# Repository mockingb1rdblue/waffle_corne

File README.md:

## Modified Corne Light PCB 
* Support for [EVQWGD001](https://www.aliexpress.com/i/4001293888953.html) horizontal encoders
* Updated Alps switch footprints to use per-key LEDs 
* PCBs have not been tested yet

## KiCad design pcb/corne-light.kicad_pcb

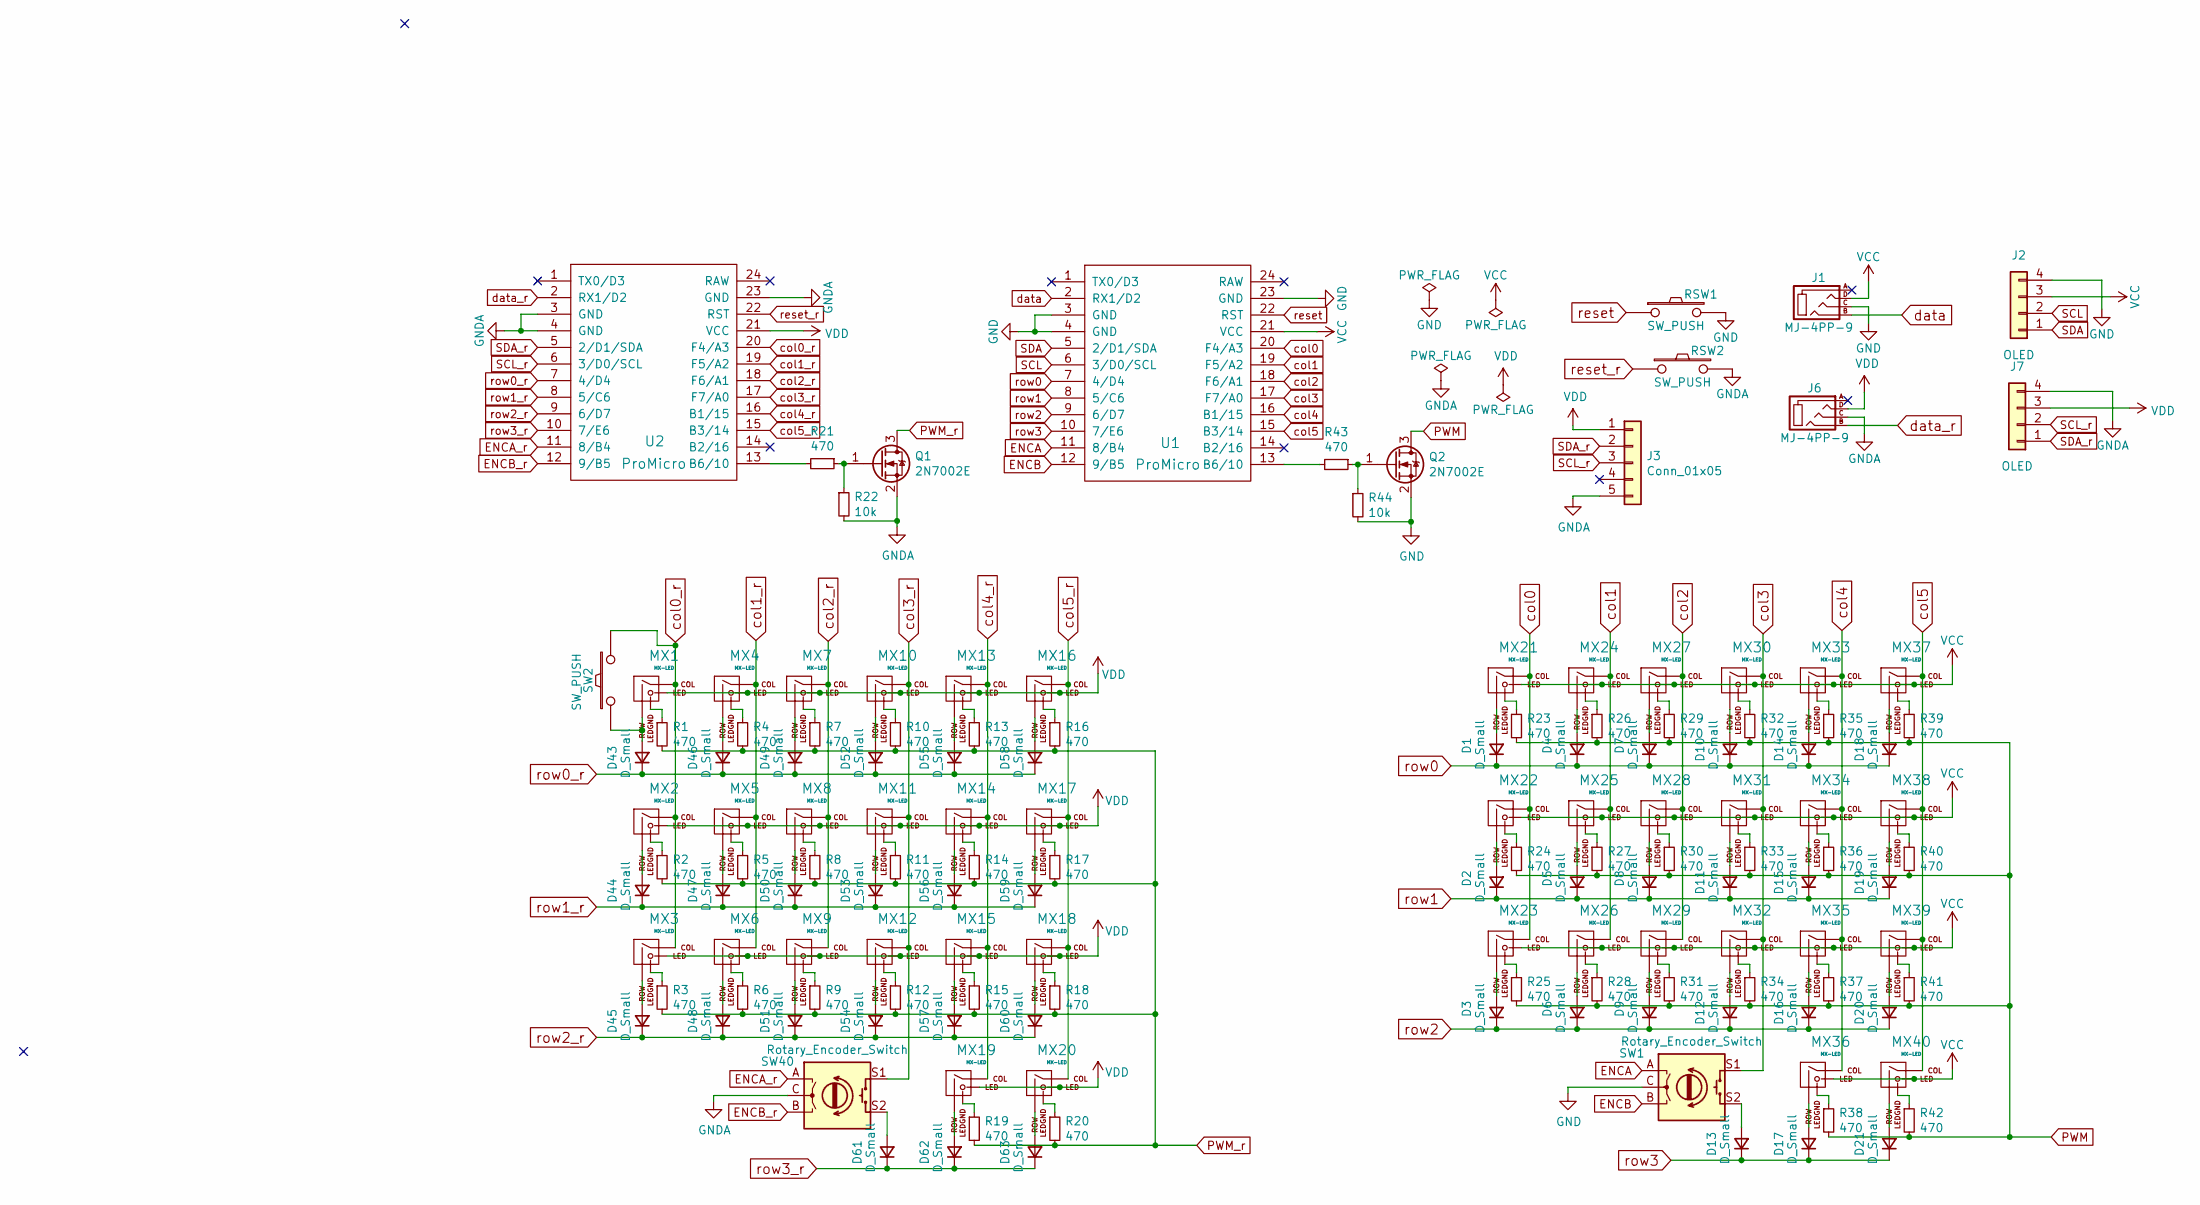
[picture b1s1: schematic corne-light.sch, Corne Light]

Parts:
D1: D_Small; Diode-hybrid-3pad
D2, D3, D4, D5, D6, D7, D8, D9, D10, D11, D12, D13, D14, D15, D16, D17, D18, D19, D20, D21, D43, D44, D45, D46, D47, D48, D49, D50, D51, D52, D53, D54, D55, D56, D57, D58, D59, D60, D61, D62, D63: D_Small; Diode-Hybrid-Back
J1, J6: MJ-4PP-9; MJ-4PP-9_1side
J2, J7: OLED; OLED_1side
J3: Conn_01x05; pimoroni_left_side_mount
MX1, MX2, MX3, MX4, MX5, MX6, MX7, MX8, MX9, MX10, MX11, MX12, MX13, MX14, MX15, MX16, MX17, MX18, MX19, MX21, MX22, MX23, MX24, MX25, MX26, MX27, MX28, MX29, MX30, MX31, MX32, MX33, MX34, MX35, MX36, MX37, MX38, MX39: MX-LED; ALPS-1U-LED
MX20, MX40: MX-LED; ALPS-1.5U-LED
Q1, Q2: 2N7002E; SOT-23
R1, R2, R3, R4, R5, R6, R7, R8, R9, R10, R11, R12, R13, R14, R15, R16, R17, R18, R19, R20, R21, R23, R24, R25, R26, R27, R28, R29, R30, R31, R32, R33, R34, R35, R36, R37, R38, R39, R40, R41, R42, R43: 470; R_0805
R22, R44: 10k; R_0805
RSW1, RSW2: SW_PUSH; ResetSW_1side
SW1, SW40: Rotary_Encoder_Switch; RollerEncoder_Panasonic_EVQWGD001
SW2: SW_PUSH; MX-1U
U1, U2: ProMicro; ProMicro_v3

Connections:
DIN: U1.1 (TX0/D3)
DIN_r: U2.1 (TX0/D3)
ENCA: SW1.A, U1.11 (8/B4)
ENCA_r: SW40.A, U2.11 (8/B4)
ENCB: SW1.B, U1.12 (9/B5)
ENCB_r: SW40.B, U2.12 (9/B5)
GND: J1.C, J2.4, Q2.2 (S), R44.2, RSW1.2, SW1.C, SW1.D, U1.3 (GND), U1.4 (GND), U1.23 (GND)
GNDA: J3.5, J6.C, J7.4, Q1.2 (S), R22.2, RSW2.2, SW40.C, SW40.D, U2.3 (GND), U2.4 (GND), U2.23 (GND)
unnamed: D1.2 (A), MX21.2 (ROW)
unnamed: D2.2 (A), MX22.2 (ROW)
unnamed: D3.2 (A), MX23.2 (ROW)
unnamed: D4.2 (A), MX24.2 (ROW)
unnamed: D5.2 (A), MX25.2 (ROW)
unnamed: D6.2 (A), MX26.2 (ROW)
unnamed: D7.2 (A), MX27.2 (ROW)
unnamed: D8.2 (A), MX28.2 (ROW)
unnamed: D9.2 (A), MX29.2 (ROW)
unnamed: D10.2 (A), MX30.2 (ROW)
unnamed: D11.2 (A), MX31.2 (ROW)
unnamed: D12.2 (A), MX32.2 (ROW)
unnamed: D13.2 (A), SW1.S2
unnamed: D14.2 (A), MX33.2 (ROW)
unnamed: D15.2 (A), MX34.2 (ROW)
unnamed: D16.2 (A), MX35.2 (ROW)
unnamed: D17.2 (A), MX36.2 (ROW)
unnamed: D18.2 (A), MX37.2 (ROW)
unnamed: D19.2 (A), MX38.2 (ROW)
unnamed: D20.2 (A), MX39.2 (ROW)
unnamed: D21.2 (A), MX40.2 (ROW)
unnamed: D43.2 (A), MX1.2 (ROW), SW2.1
unnamed: D44.2 (A), MX2.2 (ROW)
unnamed: D45.2 (A), MX3.2 (ROW)
unnamed: D46.2 (A), MX4.2 (ROW)
unnamed: D47.2 (A), MX5.2 (ROW)
unnamed: D48.2 (A), MX6.2 (ROW)
unnamed: D49.2 (A), MX7.2 (ROW)
unnamed: D50.2 (A), MX8.2 (ROW)
unnamed: D51.2 (A), MX9.2 (ROW)
unnamed: D52.2 (A), MX10.2 (ROW)
unnamed: D53.2 (A), MX11.2 (ROW)
unnamed: D54.2 (A), MX12.2 (ROW)
unnamed: D55.2 (A), MX13.2 (ROW)
unnamed: D56.2 (A), MX14.2 (ROW)
unnamed: D57.2 (A), MX15.2 (ROW)
unnamed: D58.2 (A), MX16.2 (ROW)
unnamed: D59.2 (A), MX17.2 (ROW)
unnamed: D60.2 (A), MX18.2 (ROW)
unnamed: D61.2 (A), SW40.S2
unnamed: D62.2 (A), MX19.2 (ROW)
unnamed: D63.2 (A), MX20.2 (ROW)
unnamed: MX1.4 (LEDGND), R1.1
unnamed: MX2.4 (LEDGND), R2.1
unnamed: MX3.4 (LEDGND), R3.1
unnamed: MX4.4 (LEDGND), R4.1
unnamed: MX5.4 (LEDGND), R5.1
unnamed: MX6.4 (LEDGND), R6.1
unnamed: MX7.4 (LEDGND), R7.1
unnamed: MX8.4 (LEDGND), R8.1
unnamed: MX9.4 (LEDGND), R9.1
unnamed: MX10.4 (LEDGND), R10.1
unnamed: MX11.4 (LEDGND), R11.1
unnamed: MX12.4 (LEDGND), R12.1
unnamed: MX13.4 (LEDGND), R13.1
unnamed: MX14.4 (LEDGND), R14.1
unnamed: MX15.4 (LEDGND), R15.1
unnamed: MX16.4 (LEDGND), R16.1
unnamed: MX17.4 (LEDGND), R17.1
unnamed: MX18.4 (LEDGND), R18.1
unnamed: MX19.4 (LEDGND), R19.1
unnamed: MX20.4 (LEDGND), R20.1
unnamed: MX21.4 (LEDGND), R23.1
unnamed: MX22.4 (LEDGND), R24.1
unnamed: MX23.4 (LEDGND), R25.1
unnamed: MX24.4 (LEDGND), R26.1
unnamed: MX25.4 (LEDGND), R27.1
unnamed: MX26.4 (LEDGND), R28.1
unnamed: MX27.4 (LEDGND), R29.1
unnamed: MX28.4 (LEDGND), R30.1
unnamed: MX29.4 (LEDGND), R31.1
unnamed: MX30.4 (LEDGND), R32.1
unnamed: MX31.4 (LEDGND), R33.1
unnamed: MX32.4 (LEDGND), R34.1
unnamed: MX33.4 (LEDGND), R35.1
unnamed: MX34.4 (LEDGND), R36.1
unnamed: MX35.4 (LEDGND), R37.1
unnamed: MX36.4 (LEDGND), R38.1
unnamed: MX37.4 (LEDGND), R39.1
unnamed: MX38.4 (LEDGND), R40.1
unnamed: MX39.4 (LEDGND), R41.1
unnamed: MX40.4 (LEDGND), R42.1
unnamed: Q1.1 (G), R21.1, R22.1
unnamed: Q2.1 (G), R43.1, R44.1
unnamed: R21.2, U2.13 (B6/10)
unnamed: R43.2, U1.13 (B6/10)
PWM: Q2.3 (D), R23.2, R24.2, R25.2, R26.2, R27.2, R28.2, R29.2, R30.2, R31.2, R32.2, R33.2, R34.2, R35.2, R36.2, R37.2, R38.2, R39.2, R40.2, R41.2, R42.2
PWM_r: Q1.3 (D), R1.2, R2.2, R3.2, R4.2, R5.2, R6.2, R7.2, R8.2, R9.2, R10.2, R11.2, R12.2, R13.2, R14.2, R15.2, R16.2, R17.2, R18.2, R19.2, R20.2
SCL: J2.2, U1.6 (3/D0/SCL)
SCL_r: J3.3, J7.2, U2.6 (3/D0/SCL)
SDA: J2.1, U1.5 (2/D1/SDA)
SDA_r: J3.2, J7.1, U2.5 (2/D1/SDA)
VCC: J1.D, J2.3, MX21.3 (LED), MX22.3 (LED), MX23.3 (LED), MX24.3 (LED), MX25.3 (LED), MX26.3 (LED), MX27.3 (LED), MX28.3 (LED), MX29.3 (LED), MX30.3 (LED), MX31.3 (LED), MX32.3 (LED), MX33.3 (LED), MX34.3 (LED), MX35.3 (LED), MX36.3 (LED), MX37.3 (LED), MX38.3 (LED), MX39.3 (LED), MX40.3 (LED), U1.21 (VCC)
VDD: J3.1, J6.D, J7.3, MX1.3 (LED), MX2.3 (LED), MX3.3 (LED), MX4.3 (LED), MX5.3 (LED), MX6.3 (LED), MX7.3 (LED), MX8.3 (LED), MX9.3 (LED), MX10.3 (LED), MX11.3 (LED), MX12.3 (LED), MX13.3 (LED), MX14.3 (LED), MX15.3 (LED), MX16.3 (LED), MX17.3 (LED), MX18.3 (LED), MX19.3 (LED), MX20.3 (LED), U2.21 (VCC)
col0: MX21.1 (COL), MX22.1 (COL), MX23.1 (COL), U1.20 (F4/A3)
col0_r: MX1.1 (COL), MX2.1 (COL), MX3.1 (COL), SW2.2, U2.20 (F4/A3)
col1: MX24.1 (COL), MX25.1 (COL), MX26.1 (COL), U1.19 (F5/A2)
col1_r: MX4.1 (COL), MX5.1 (COL), MX6.1 (COL), U2.19 (F5/A2)
col2: MX27.1 (COL), MX28.1 (COL), MX29.1 (COL), U1.18 (F6/A1)
col2_r: MX7.1 (COL), MX8.1 (COL), MX9.1 (COL), U2.18 (F6/A1)
col3: MX30.1 (COL), MX31.1 (COL), MX32.1 (COL), SW1.S1, U1.17 (F7/A0)
col3_r: MX10.1 (COL), MX11.1 (COL), MX12.1 (COL), SW40.S1, U2.17 (F7/A0)
col4: MX33.1 (COL), MX34.1 (COL), MX35.1 (COL), MX36.1 (COL), U1.16 (B1/15)
col4_r: MX13.1 (COL), MX14.1 (COL), MX15.1 (COL), MX19.1 (COL), U2.16 (B1/15)
col5: MX37.1 (COL), MX38.1 (COL), MX39.1 (COL), MX40.1 (COL), U1.15 (B3/14)
col5_r: MX16.1 (COL), MX17.1 (COL), MX18.1 (COL), MX20.1 (COL), U2.15 (B3/14)
data: J1.B, U1.2 (RX1/D2)
data_r: J6.B, U2.2 (RX1/D2)
reset: RSW1.1, U1.22 (RST)
reset_r: RSW2.1, U2.22 (RST)
row0: D1.1 (K), D4.1 (K), D7.1 (K), D10.1 (K), D14.1 (K), D18.1 (K), U1.7 (4/D4)
row0_r: D43.1 (K), D46.1 (K), D49.1 (K), D52.1 (K), D55.1 (K), D58.1 (K), U2.7 (4/D4)
row1: D2.1 (K), D5.1 (K), D8.1 (K), D11.1 (K), D15.1 (K), D19.1 (K), U1.8 (5/C6)
row1_r: D44.1 (K), D47.1 (K), D50.1 (K), D53.1 (K), D56.1 (K), D59.1 (K), U2.8 (5/C6)
row2: D3.1 (K), D6.1 (K), D9.1 (K), D12.1 (K), D16.1 (K), D20.1 (K), U1.9 (6/D7)
row2_r: D45.1 (K), D48.1 (K), D51.1 (K), D54.1 (K), D57.1 (K), D60.1 (K), U2.9 (6/D7)
row3: D13.1 (K), D17.1 (K), D21.1 (K), U1.10 (7/E6)
row3_r: D61.1 (K), D62.1 (K), D63.1 (K), U2.10 (7/E6)

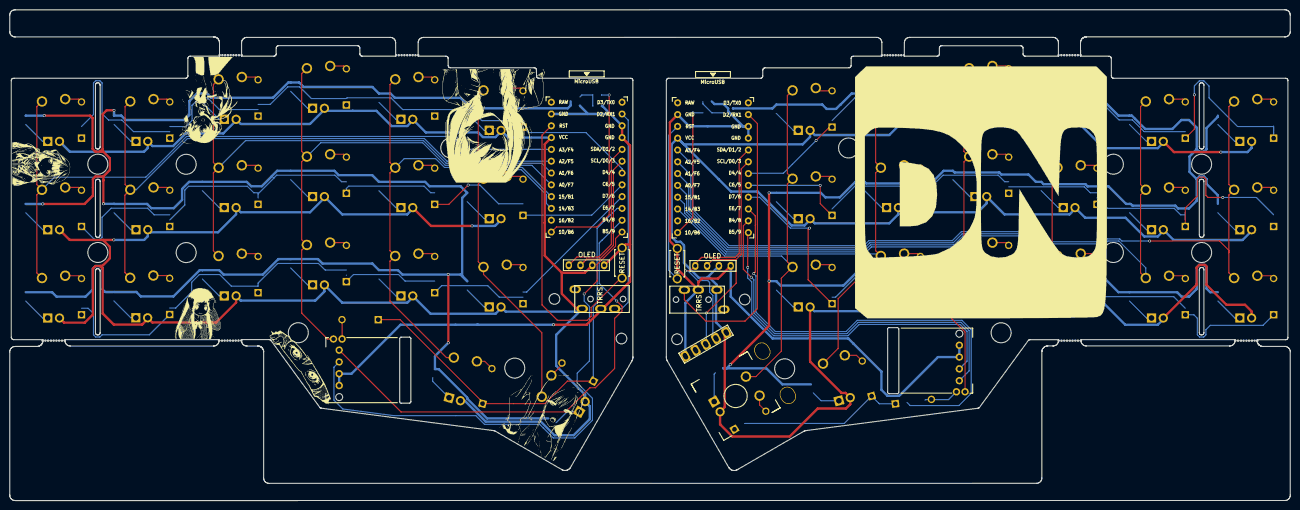
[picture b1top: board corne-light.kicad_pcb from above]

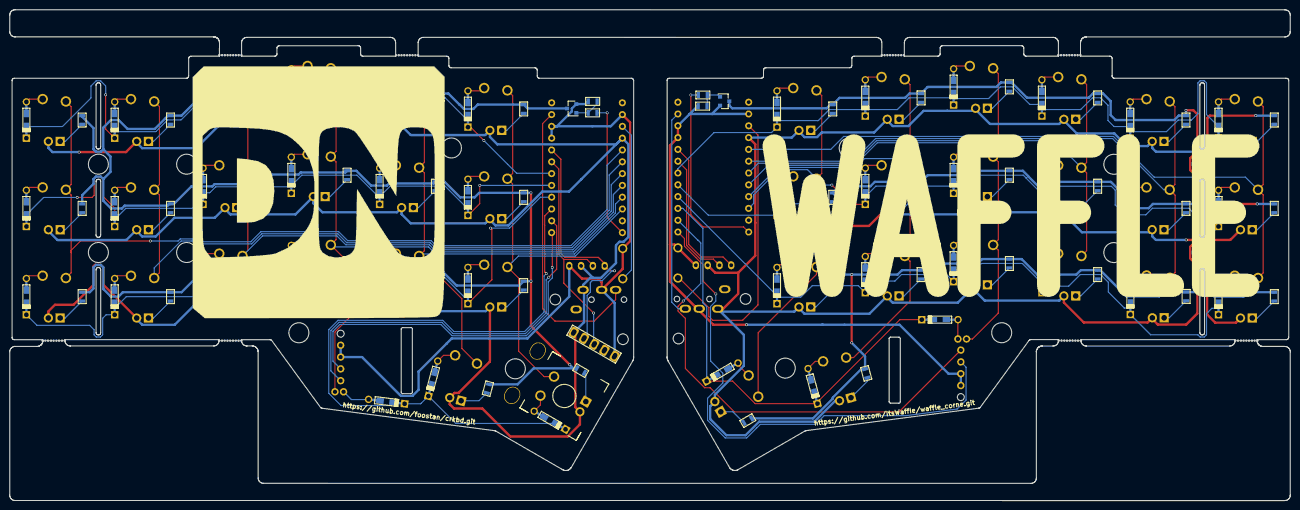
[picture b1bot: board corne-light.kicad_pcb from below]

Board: 2 copper layers, 275.5 x 105.6 mm, 165 parts (63 on the bottom side), 124 nets.

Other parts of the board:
J5, J5#2, J5#3, J5#4, J5#5, J5#6, J5#7, J5#8: Breakaway_Tabs
Ref**: Val**; spacer_m2
Ref**#2, Ref**#3, Ref**#4, Ref**#9, Ref**#10, Ref**#11, Ref**#12, Ref**#13, Ref**#14, Ref**#15, Ref**#16, Ref**#17, Ref**#18: Val**; spacer_m2
Ref**#5, Ref**#6, Ref**#7, Ref**#8: Val**; thread_m2

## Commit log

2021-01-26 Overhaul
2021-02-04 Combo Update
2021-02-04 Remove useless macros
2021-02-15 Add more oled stuff
2021-02-16 Image Update
2021-03-05 Firmware Updated to AVR Corne :3
2021-05-12 Add initial pcb stuff
2021-05-12 Add initial readme and pcb image
2021-05-12 Update rotation and proper grounding
2021-05-12 finish alps and leds on right half
2021-05-12 add alps and leds to left half
2021-05-13 Finish RGB
2021-05-13 Remove RGB and add a new image
2021-05-19 Fix mosfet and add add silkscreen stuff
2021-05-19 I dunno what this
2021-05-19 Add trackball support
2021-05-19 Remove references from silkscreen
2021-05-24 Fix vcc trace
2021-05-25 Fix DRC errors and rotate encoders
2021-06-02 Remove unecessary flag in schematic
